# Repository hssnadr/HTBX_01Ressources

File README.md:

# HTBX_01Ressources
Hitbox documentation and file ressources

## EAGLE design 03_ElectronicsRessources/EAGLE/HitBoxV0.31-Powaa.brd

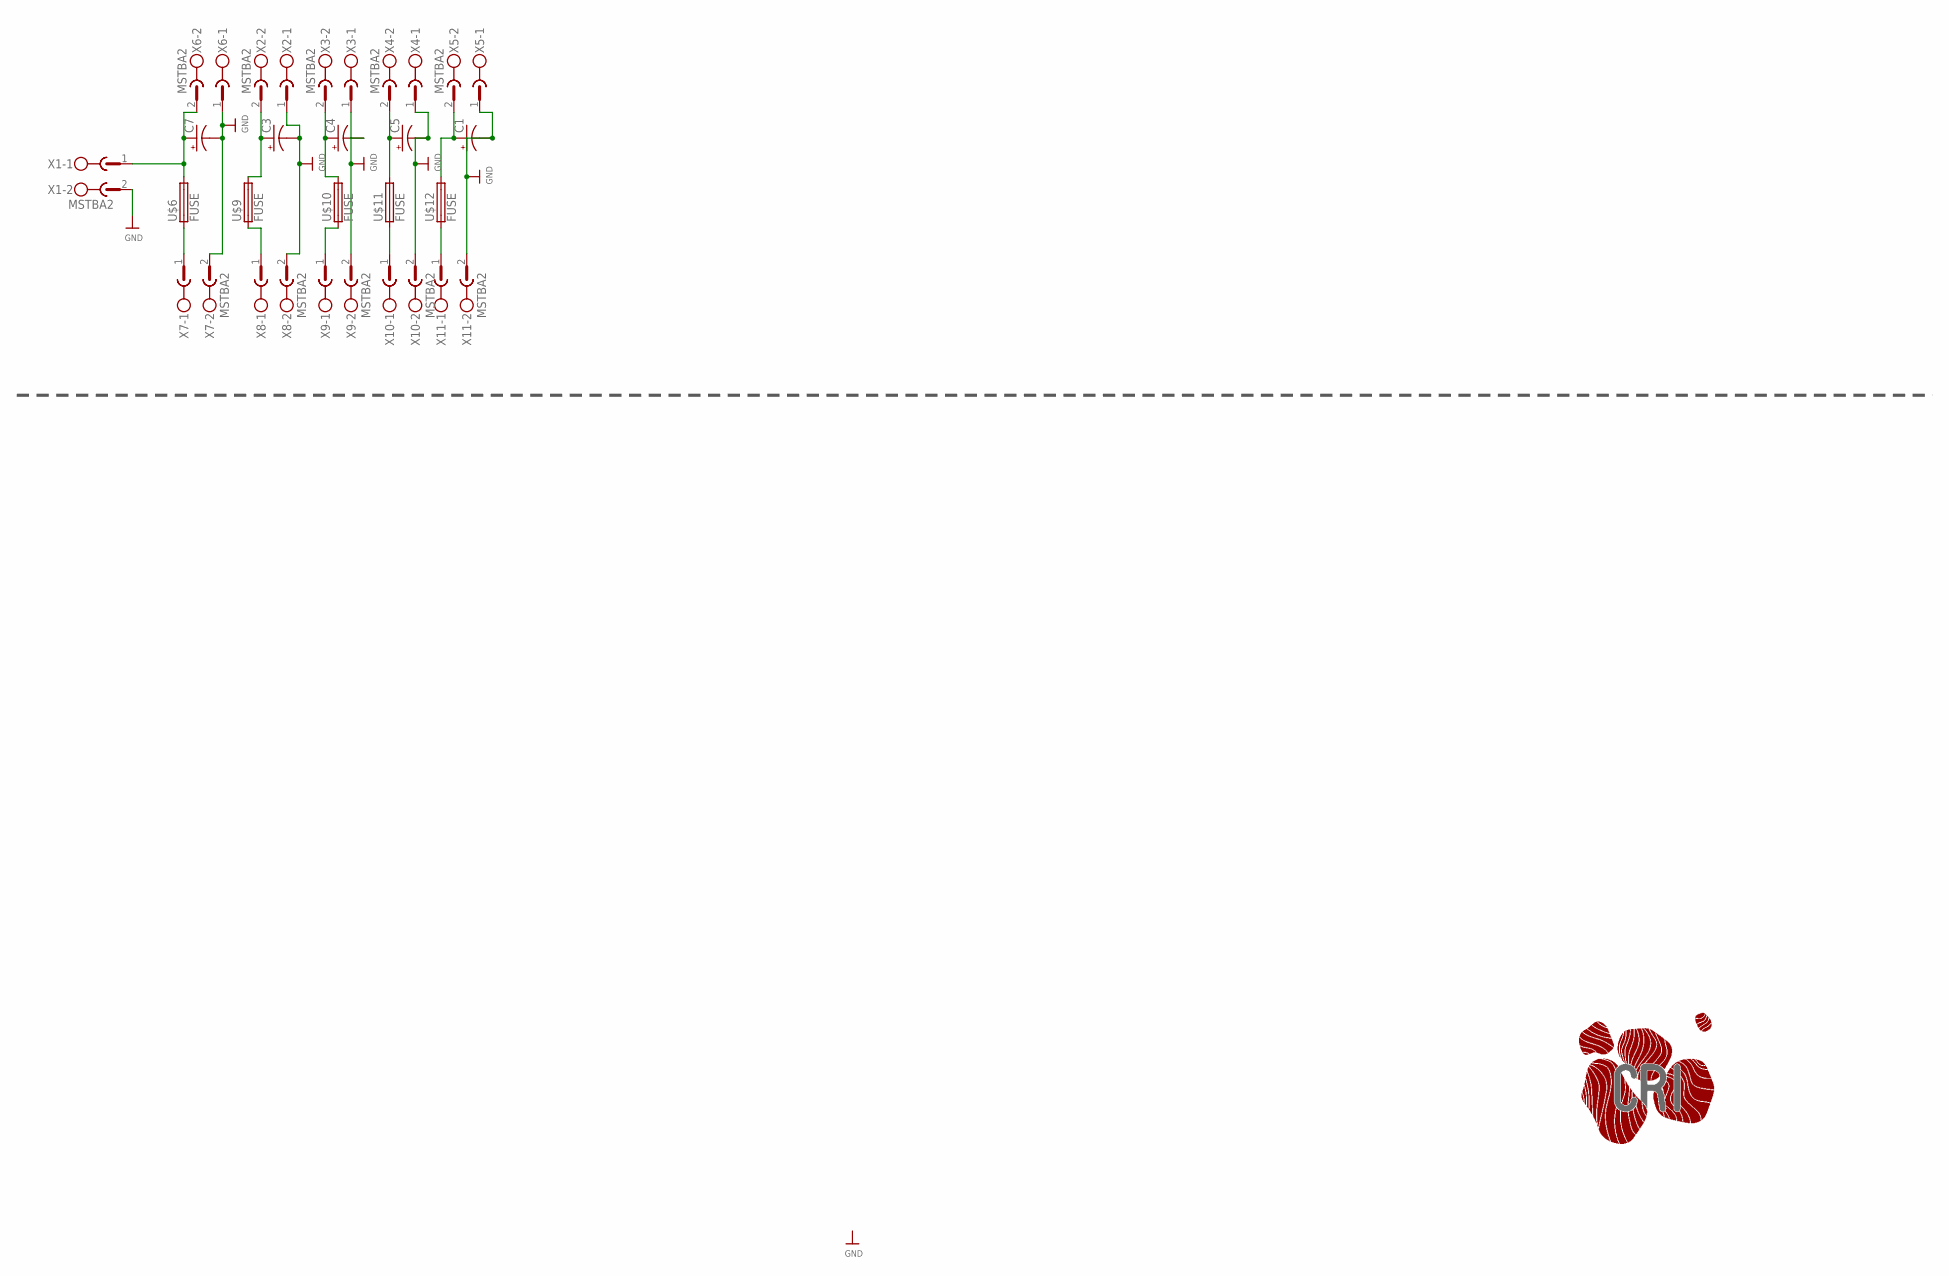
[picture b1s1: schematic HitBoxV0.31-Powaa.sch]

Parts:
C1, C3, C4, C5, C7: CPOL-USE2,5-6E; E2,5-6E
U$6, U$9, U$10, U$11, U$12: FUSE; KEYSTONE-AUTO-FUSE
U$7: LOGO-CRI-NEW-130MMX30MM-TPLACE; LOGO_CRI-NEW-BMP30MM-TOP
X1, X2, X3, X4, X5, X6, X7, X8, X9, X10, X11: MSTBA2

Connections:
GND: C1.-, C3.-, C4.-, C5.-, C7.-, X1.2, X2.1, X3.1, X4.1, X5.1, X6.1, X7.2, X8.2, X9.2, X10.2, X11.2
unnamed: C7.+, U$6.P$3 (2), U$6.P$4 (2), X1.1, X6.2
unnamed: C3.+, U$9.P$3 (2), U$9.P$4 (2), X2.2
unnamed: C4.+, U$10.P$3 (2), U$10.P$4 (2), X3.2
unnamed: C5.+, U$11.P$3 (2), U$11.P$4 (2), X4.2
unnamed: C1.+, U$12.P$3 (2), U$12.P$4 (2), X5.2
unnamed: U$6.P$1 (1), U$6.P$2 (1), X7.1
unnamed: U$9.P$1 (1), U$9.P$2 (1), X8.1
unnamed: U$10.P$1 (1), U$10.P$2 (1), X9.1
unnamed: U$11.P$1 (1), U$11.P$2 (1), X10.1
unnamed: U$12.P$1 (1), U$12.P$2 (1), X11.1

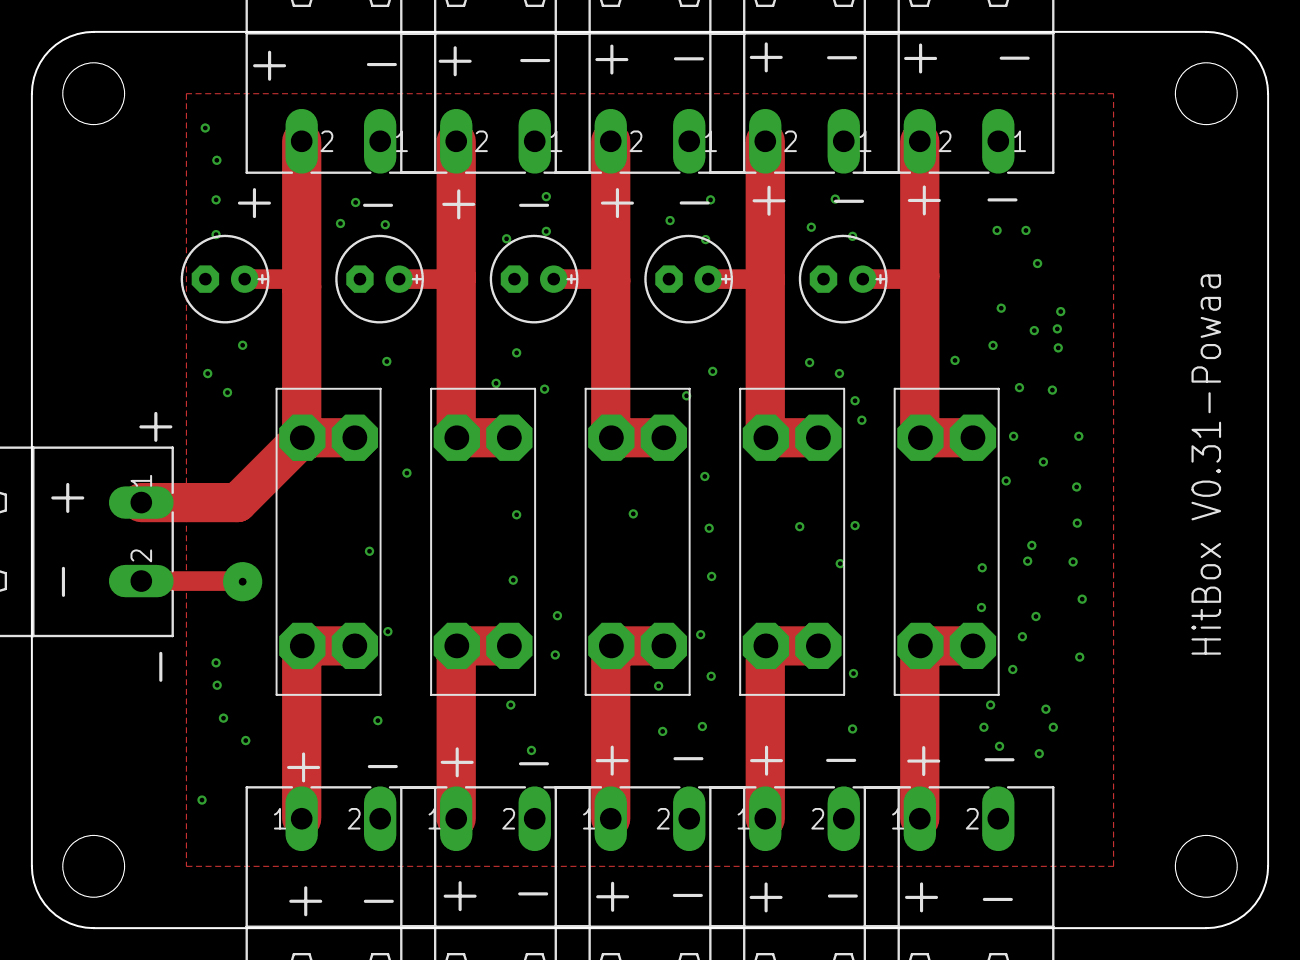
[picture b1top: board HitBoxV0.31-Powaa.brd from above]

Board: 2 copper layers, 80.0 x 58.0 mm, 22 parts (1 on the bottom side), 11 nets.

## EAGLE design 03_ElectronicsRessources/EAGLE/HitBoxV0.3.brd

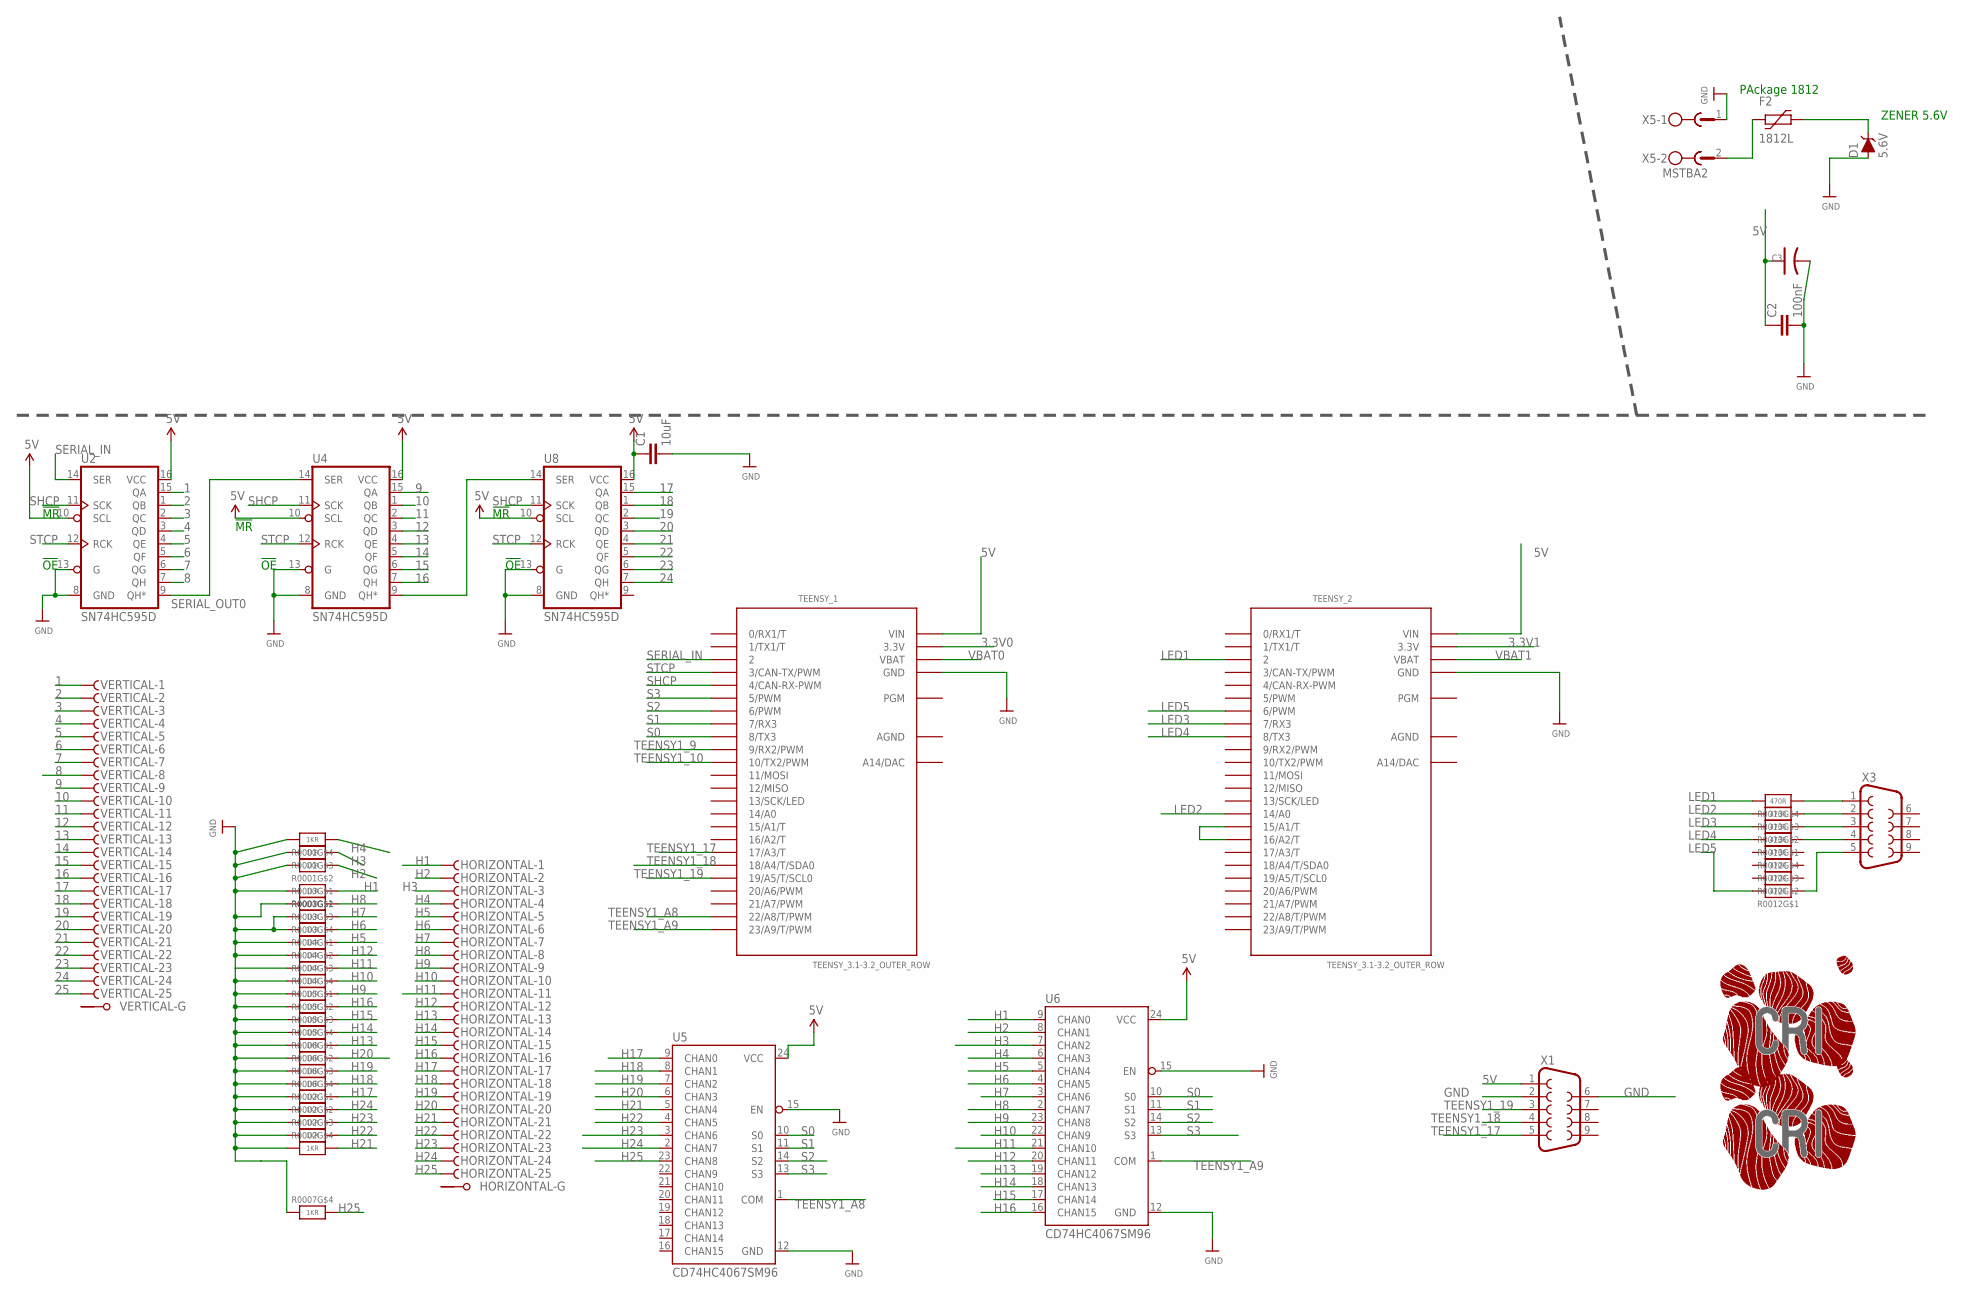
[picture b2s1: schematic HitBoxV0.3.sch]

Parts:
C1: 10uF; 0402-CAP
C2: 100nF; C0805
C3: C-POLAR8MMX10MM; CAP-POL-8MMX10MM
D1: 5.6V; SOD-323
F2: 1812L
HORIZONTAL: F25VPS; F25VP
R0001, R0002, R0003, R0004, R0005, R0006, R0007: 1KR; RESPACK_4X0603
R0012, R0013: 470R; RESPACK_4X0603
TEENSY_1, TEENSY_2: TEENSY_3.1-3.2_OUTER_ROW; TEENSY_3.0-3.2&LC_OUTER_ROW
U2, U4, U8: SN74HC595D; SO16
U5, U6: CD74HC4067SM96; SSOP24
U$8: LOGO-CRI-NEW-150MM-TOP-TPLACE; LOGO_CRI-NEW-BMP50MM-TOP
U$10: LOGO-CRI-NEW-130MMX30MM-TPLACE; LOGO_CRI-NEW-BMP30MM-TOP
VERTICAL: F25VPS; F25VP
X1, X3: F09VP
X5: MSTBA2

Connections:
1: U2.15 (QA), VERTICAL.1 (F)
2: U2.1 (QB), VERTICAL.2 (F)
3: U2.2 (QC), VERTICAL.3 (F)
3.3V0: TEENSY_1.3.3V, TEENSY_1.3.3V1 (3.3V)
3.3V1: TEENSY_2.3.3V, TEENSY_2.3.3V1 (3.3V)
4: U2.3 (QD), VERTICAL.4 (F)
5: U2.4 (QE), VERTICAL.5 (F)
5V: C1.1, C2.1, C3.+ (1), D1.C, F2.P$2 (2), TEENSY_1.VIN, TEENSY_2.VIN, U2.10 (SCL), U2.16 (VCC), U4.10 (SCL), U4.16 (VCC), U5.24 (VCC), U6.24 (VCC), U8.10 (SCL), U8.16 (VCC), X1.1
6: U2.5 (QF), VERTICAL.6 (F)
7: U2.6 (QG), VERTICAL.7 (F)
8: U2.7 (QH), VERTICAL.8 (F)
9: U4.15 (QA), VERTICAL.9 (F)
10: U4.1 (QB), VERTICAL.10 (F)
11: U4.2 (QC), VERTICAL.11 (F)
12: U4.3 (QD), VERTICAL.12 (F)
13: U4.4 (QE), VERTICAL.13 (F)
14: U4.5 (QF), VERTICAL.14 (F)
15: U4.6 (QG), VERTICAL.15 (F)
16: U4.7 (QH), VERTICAL.16 (F)
17: U8.15 (QA), VERTICAL.17 (F)
18: U8.1 (QB), VERTICAL.18 (F)
19: U8.2 (QC), VERTICAL.19 (F)
20: U8.3 (QD), VERTICAL.20 (F)
21: U8.4 (QE), VERTICAL.21 (F)
22: U8.5 (QF), VERTICAL.22 (F)
23: U8.6 (QG), VERTICAL.23 (F)
24: U8.7 (QH), VERTICAL.24 (F)
25: VERTICAL.25 (F)
AGND: TEENSY_1.AGND, TEENSY_2.AGND
GND: C1.2, C2.2, C3.- (2), D1.A, R0001.5 (2), R0001.6 (2), R0001.7 (2), R0001.8 (2), R0002.1, R0002.2 (1), R0002.3 (1), R0002.4 (1), R0003.1, R0003.2 (1), R0003.3 (1), R0003.4 (1), R0004.1, R0004.2 (1), R0004.3 (1), R0004.4 (1), R0005.1, R0005.2 (1), R0005.3 (1), R0005.4 (1), R0006.1, R0006.2 (1), R0006.3 (1), R0006.4 (1), R0007.4 (1), TEENSY_1.GND, TEENSY_1.GND1 (GND), TEENSY_2.GND, TEENSY_2.GND1 (GND), U2.8 (GND), U2.13 (G), U4.8 (GND), U4.13 (G), U5.12 (GND), U5.15 (EN), U6.12 (GND), U6.15 (EN), U8.8 (GND), U8.13 (G), X1.2, X1.6, X5.1
H1: HORIZONTAL.1 (F), R0001.1, U6.9 (CHAN0)
H2: HORIZONTAL.2 (F), R0001.2 (1), U6.8 (CHAN1)
H3: HORIZONTAL.3 (F), R0001.3 (1), U6.7 (CHAN2)
H4: HORIZONTAL.4 (F), R0001.4 (1), U6.6 (CHAN3)
H5: HORIZONTAL.5 (F), R0003.5 (2), U6.5 (CHAN4)
H6: HORIZONTAL.6 (F), R0003.6 (2), U6.4 (CHAN5)
H7: HORIZONTAL.7 (F), R0003.7 (2), U6.3 (CHAN6)
H8: HORIZONTAL.8 (F), R0003.8 (2), U6.2 (CHAN7)
H9: HORIZONTAL.9 (F), R0004.5 (2), U6.23 (CHAN8)
H10: HORIZONTAL.10 (F), R0004.6 (2), U6.22 (CHAN9)
H11: HORIZONTAL.11 (F), R0004.7 (2), U6.21 (CHAN10)
H12: HORIZONTAL.12 (F), R0004.8 (2), U6.20 (CHAN11)
H13: HORIZONTAL.13 (F), R0005.5 (2), U6.19 (CHAN12)
H14: HORIZONTAL.14 (F), R0005.6 (2), U6.18 (CHAN13)
H15: HORIZONTAL.15 (F), R0005.7 (2), U6.17 (CHAN14)
H16: HORIZONTAL.16 (F), R0005.8 (2), U6.16 (CHAN15)
H17: HORIZONTAL.17 (F), R0006.5 (2), U5.9 (CHAN0)
H18: HORIZONTAL.18 (F), R0006.6 (2), U5.8 (CHAN1)
H19: HORIZONTAL.19 (F), R0006.7 (2), U5.7 (CHAN2)
H20: HORIZONTAL.20 (F), R0006.8 (2), U5.6 (CHAN3)
H21: HORIZONTAL.21 (F), R0002.5 (2), U5.5 (CHAN4)
H22: HORIZONTAL.22 (F), R0002.6 (2), U5.4 (CHAN5)
H23: HORIZONTAL.23 (F), R0002.7 (2), U5.3 (CHAN6)
H24: HORIZONTAL.24 (F), R0002.8 (2), U5.2 (CHAN7)
H25: HORIZONTAL.25 (F), R0007.5 (2), U5.23 (CHAN8)
LED1: R0013.5 (2), TEENSY_2.2
LED2: R0013.6 (2), TEENSY_2.14/A0
LED3: R0013.7 (2), TEENSY_2.7 (7/RX3)
LED4: R0013.8 (2), TEENSY_2.8 (8/TX3)
LED5: R0012.8 (2), TEENSY_2.6 (6/PWM)
unnamed: R0013.4 (1), X3.1
unnamed: R0013.3 (1), X3.2
unnamed: U4.9 (QH*), U8.14 (SER)
unnamed: R0013.2 (1), X3.3
unnamed: R0013.1, X3.4
unnamed: TEENSY_2.15/A1 (15/A1/T), TEENSY_2.16/A2 (16/A2/T)
unnamed: F2.P$1 (1), X5.2
unnamed: R0012.1, X3.5
S0: TEENSY_1.8 (8/TX3), U5.10 (S0), U6.10 (S0)
S1: TEENSY_1.7 (7/RX3), U5.11 (S1), U6.11 (S1)
S2: TEENSY_1.6 (6/PWM), U5.14 (S2), U6.14 (S2)
S3: TEENSY_1.5 (5/PWM), U5.13 (S3), U6.13 (S3)
SERIAL_IN: TEENSY_1.2, U2.14 (SER)
SERIAL_OUT0: U2.9 (QH*), U4.14 (SER)
SHCP: TEENSY_1.4 (4/CAN-RX-PWM), U2.11 (SCK), U4.11 (SCK), U8.11 (SCK)
STCP: TEENSY_1.3 (3/CAN-TX/PWM), U2.12 (RCK), U4.12 (RCK), U8.12 (RCK)
TEENSY1_9: TEENSY_1.9 (9/RX2/PWM)
TEENSY1_10: TEENSY_1.10 (10/TX2/PWM)
TEENSY1_17: TEENSY_1.17/A3 (17/A3/T), X1.5
TEENSY1_18: TEENSY_1.18/A4 (18/A4/T/SDA0), X1.4
TEENSY1_19: TEENSY_1.19/A5 (19/A5/T/SCL0), X1.3
TEENSY1_A8: TEENSY_1.22/A8 (22/A8/T/PWM), U5.1 (COM)
TEENSY1_A9: TEENSY_1.23/A9 (23/A9/T/PWM), U6.1 (COM)
VBAT0: TEENSY_1.VBAT
VBAT1: TEENSY_2.VBAT

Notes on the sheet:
!OE!
!MR!
PAckage 1812
ZENER 5.6V

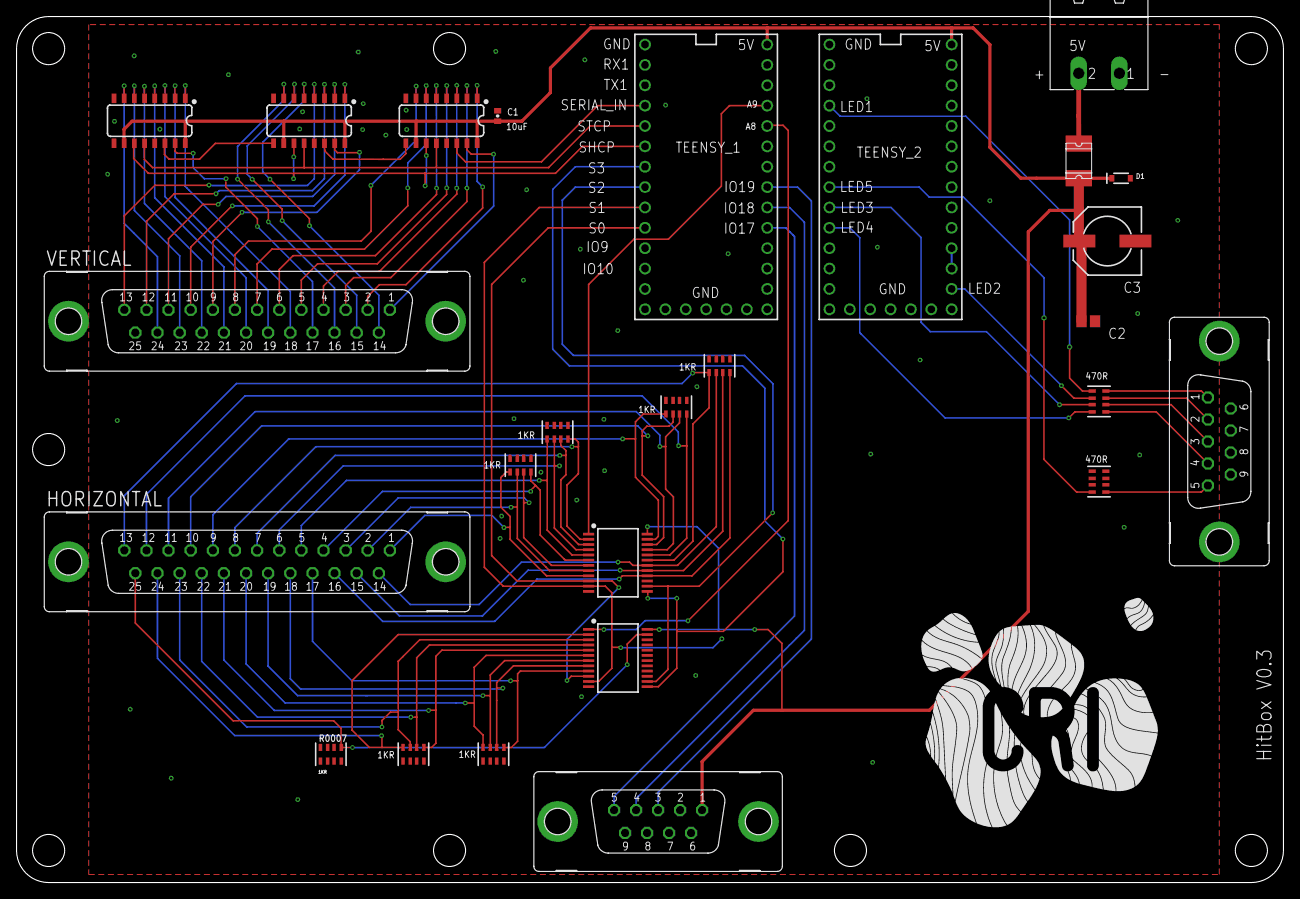
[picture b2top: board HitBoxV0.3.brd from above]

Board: 2 copper layers, 158.0 x 108.0 mm, 28 parts (1 on the bottom side), 80 nets.

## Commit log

2020-06-19 init
2020-06-22 hitbox assembly init
2020-06-23 catia_innerCase
2020-06-24 update Catia
2020-06-25 update Hitbox assembly
2020-06-28 update_catia
2020-07-01 update_wires
2020-07-10 update_catia_assemblyupdate
2020-07-21 update_namaste
2020-07-22 update_*-*
2020-07-24 update_screws1
2020-07-25 Hitbox_CatiaProduct_v1
2020-08-21 clean cable 1
2020-08-21 Catia_goodWire
2020-08-24 catia_wirepowerboard
2020-08-25 catia clean
2020-08-26 catia_ledsmooth
2020-08-26 testfdp
2020-08-26 Revert "testfdp"
    This reverts commit c0a527d713aa96d3e811c7f13a6af79030394948.
2020-08-26 Revert "Revert "testfdp""
    This reverts commit ab473c10f75899fee0d607c167fabfc2b384264c.
2020-08-26 update_inshallah
2020-08-28 catia cut 1

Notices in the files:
parts and their libraries:
SparkFun-IC-Logic: Licensing: Creative Commons ShareAlike 4.0 International - https://creativecommons.org/licenses/by-sa/4.0
microbuilder: This work is placed in the public domain, and may be freely used for commercial and non-commercial work with the following conditions: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
